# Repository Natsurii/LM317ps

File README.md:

# LM317ps
An AC to DC variable voltage power supply demonstrating the bridge rectification using 1N400X diode and LM317 Voltage Regulator.

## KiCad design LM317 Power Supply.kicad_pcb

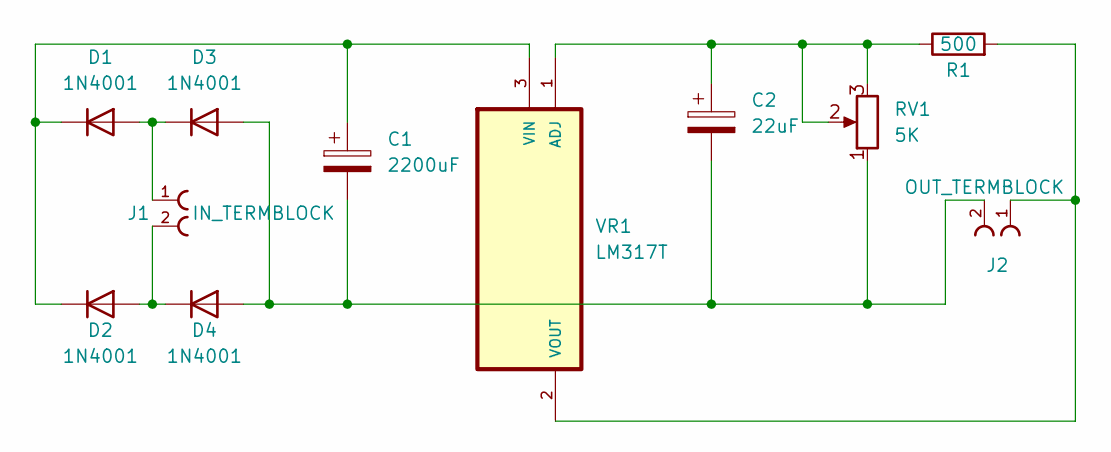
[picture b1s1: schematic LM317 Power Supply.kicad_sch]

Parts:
C1: 2200uF; C_Radial_D12.5mm_H25.0mm_P5.00mm
C2: 22uF; C_Radial_D5.0mm_H11.0mm_P2.00mm
D1, D2, D3, D4: 1N4001; D_DO-41_SOD81_P10.16mm_Horizontal
J1: IN_TERMBLOCK; 691137710002
J2: OUT_TERMBLOCK; 691137710002
R1: 500; R_Axial_DIN0204_L3.6mm_D1.6mm_P5.08mm_Horizontal
RV1: 5K; Potentiometer_Alps_RK163_Single_Horizontal
VR1: LM317T; TO254P1054X470X1955-3

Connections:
unnamed: C1.2, C2.2, D3.2 (A), D4.2 (A), J2.2, RV1.1
unnamed: C1.1, D1.1 (K), D2.1 (K), VR1.3 (VIN)
unnamed: D1.2 (A), D3.1 (K), J1.1
unnamed: D2.2 (A), D4.1 (K), J1.2
unnamed: C2.1, R1.1, RV1.2, RV1.3, VR1.1 (ADJ)
unnamed: J2.1, R1.2, VR1.2 (VOUT)

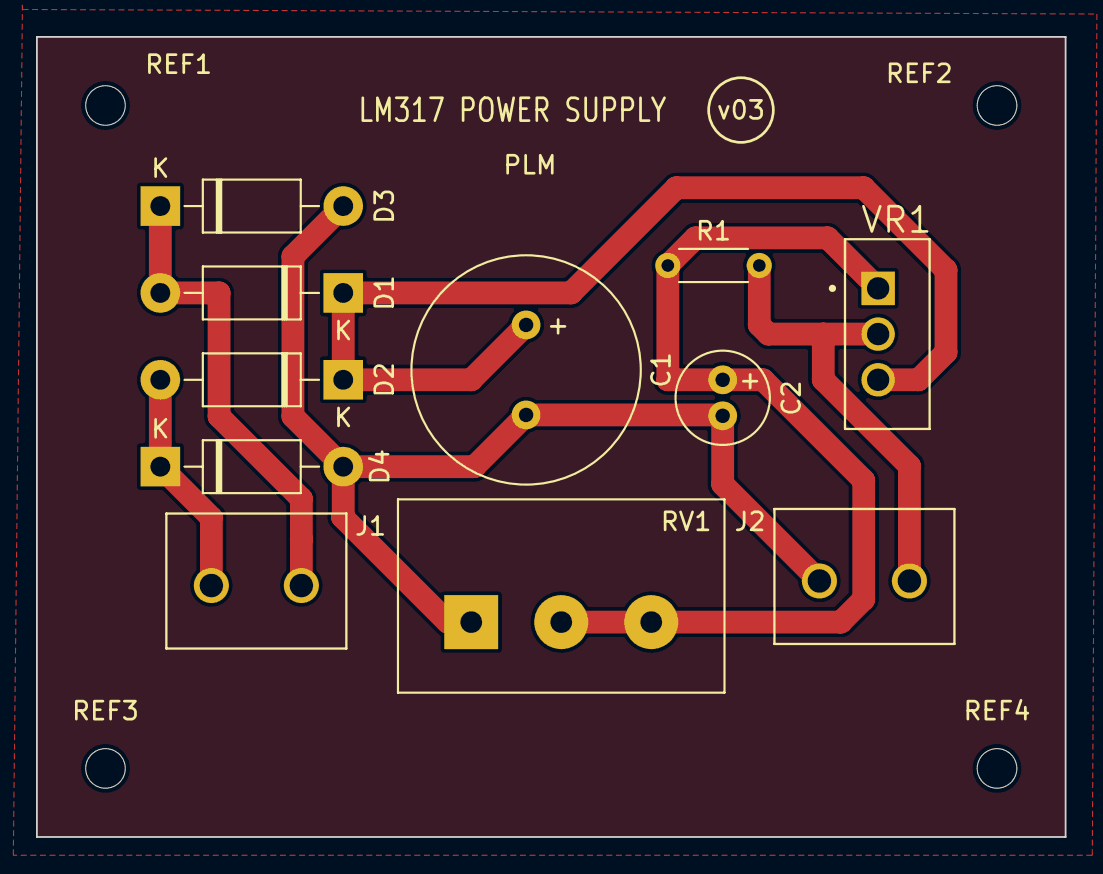
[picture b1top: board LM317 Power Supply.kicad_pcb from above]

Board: 2 copper layers, 57.2 x 44.5 mm, 15 parts (0 on the bottom side), 6 nets.

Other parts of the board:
REF1, REF2, REF3, REF4: MountingHole_2.2mm_M2

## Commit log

2023-09-23 Add README file
